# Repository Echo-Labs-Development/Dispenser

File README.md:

# Dispenser #
The dispenser will be a Quantum Manufacturing Connected Dispenser for diffrent larger items.

## BOM ##
- 1x Dispenser PCB
- 1x Control Box - Lid
- 1x Control Box - Box
- 2x Pegs
- 2x 4x2 Magnets

## Dispenable Matierials ##
- [ ] 2020 Aluminum Exstrusion
- [ ] Quantum Printer Brim
### More Planned ###

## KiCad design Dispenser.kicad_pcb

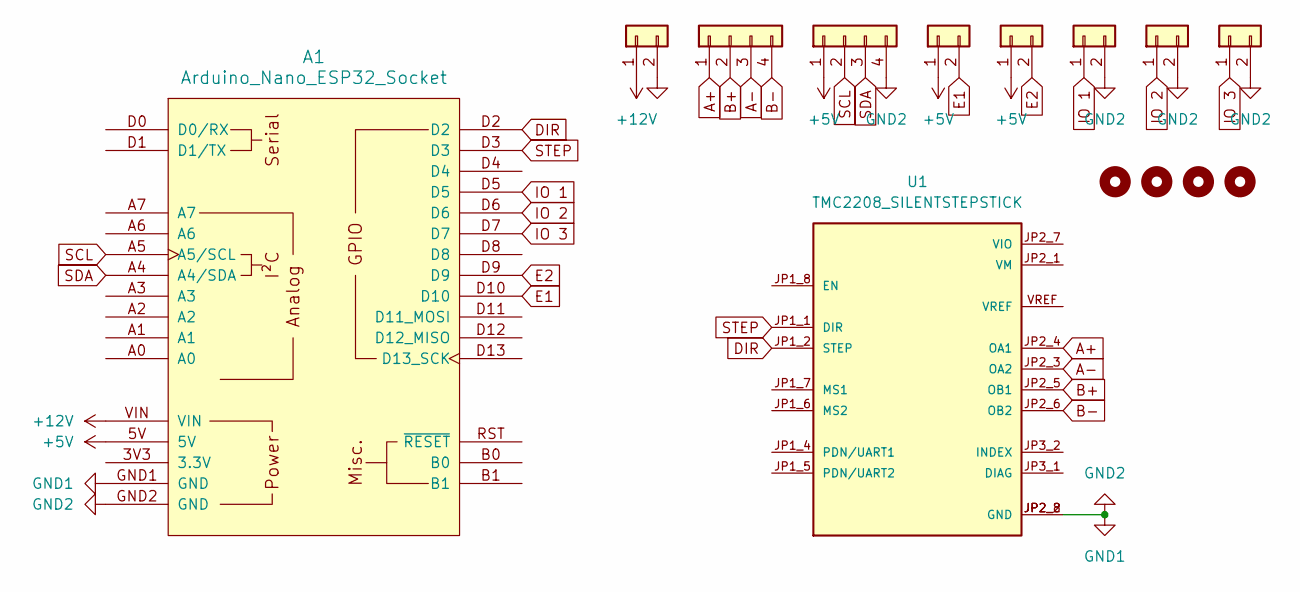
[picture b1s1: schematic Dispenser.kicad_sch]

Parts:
A1: Arduino_Nano_ESP32_Socket
E1, E2: Conn_01x02; JST_EH_B2B-EH-A_1x02_P2.50mm_Vertical
H1, H2, H3, H4: MountingHole
IO1, IO2, IO3: Conn_01x02; JST_EH_B2B-EH-A_1x02_P2.50mm_Vertical
O1: Conn_01x04; JST_EH_B4B-EH-A_1x04_P2.50mm_Vertical
P1: Conn_01x02; JST_EH_B2B-EH-A_1x02_P2.50mm_Vertical
S1: Conn_01x04; JST_EH_B4B-EH-A_1x04_P2.50mm_Vertical
U1: TMC2208_SILENTSTEPSTICK; MODULE_TMC2208_SILENTSTEPSTICK

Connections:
+5V: A1.5V, E1.1, E2.1, O1.1
+12V: A1.VIN, P1.1
A+: S1.1, U1.JP2_4 (OA1)
A-: S1.3, U1.JP2_3 (OA2)
B+: S1.2, U1.JP2_5 (OB1)
B-: S1.4, U1.JP2_6 (OB2)
DIR: A1.D2, U1.JP1_2 (STEP)
E1: A1.D10, E1.2
E2: A1.D9, E2.2
GND1: A1.GND1 (GND), A1.GND2 (GND), IO1.2, IO2.2, IO3.2, O1.4, P1.2, U1.JP2_2 (GND), U1.JP2_8 (GND)
IO 1: A1.D5, IO1.1
IO 2: A1.D6, IO2.1
IO 3: A1.D7, IO3.1
SCL: A1.A5 (A5/SCL), O1.2
SDA: A1.A4 (A4/SDA), O1.3
STEP: A1.D3, U1.JP1_1 (DIR)

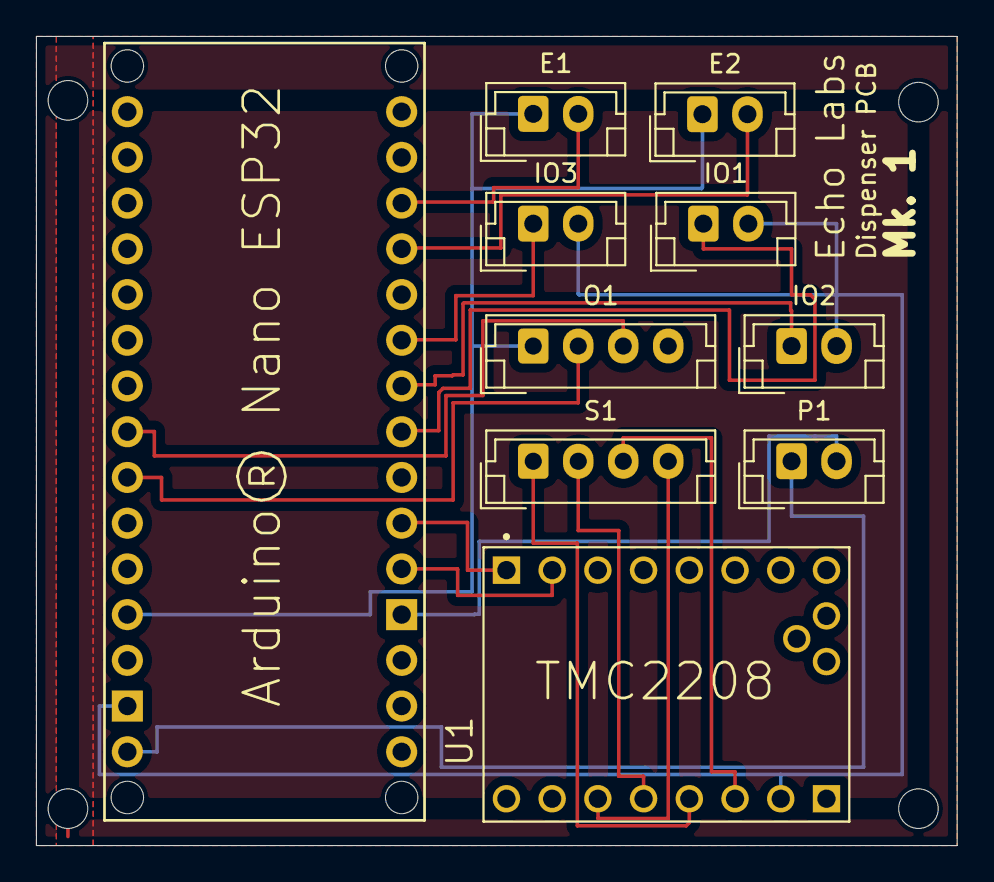
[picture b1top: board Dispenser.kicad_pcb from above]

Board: 2 copper layers, 51.1 x 44.9 mm, 14 parts (0 on the bottom side), 16 nets.

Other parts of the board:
H3#2: MountingHole; MountingHole_2.2mm_M2

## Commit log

2024-08-23 Finish Schmatic and Half of PCB
2024-08-23 Update Schematic and Finsh Board
2024-08-23 Add Mounting Holes
2024-08-23 Add 3d printed box for holding board
2024-08-23 Add hinge to box
2024-08-29 Add Screenshots
